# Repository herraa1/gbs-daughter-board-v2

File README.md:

# GBS Control Daughter Board v2

Enhance your [GBS8200](https://ramapcsx2.github.io/gbs-control/Wiki/Build-the-Hardware.html) upscaler board.

> [!WARNING]
> This is a work in progress project.
>
> An adapter based on PCB v2 Build1 has been successfully built
>
> No build instructions are yet provided
>

## Introduction

The GBS Daughter Board v2 is a companion board for the GBS8200 upscaler.
It facilitates the upgrade of an off-the-shelf GBS8200 board to a gbs-control firmware based solution, with the following main features:

* HAT-like design, simply stack the daughter board on top of the existing GBS8200
* add SCART RGB input
* add switchable HDMI output (via embedded VGA to HDMI dongle)
* add switchable sync stripper based on the LM1881
* add 3.5" jack sound output
* add switchable common or separate audio ground
* add auxiliar USB socket to optionally power external dongle
* add small OLED screen and rotary encoder for local control

## References

gbs-control
* https://github.com/ramapcsx2/gbs-control

GBS-C AIO
* https://github.com/amoore2600/GBS-C_AIO

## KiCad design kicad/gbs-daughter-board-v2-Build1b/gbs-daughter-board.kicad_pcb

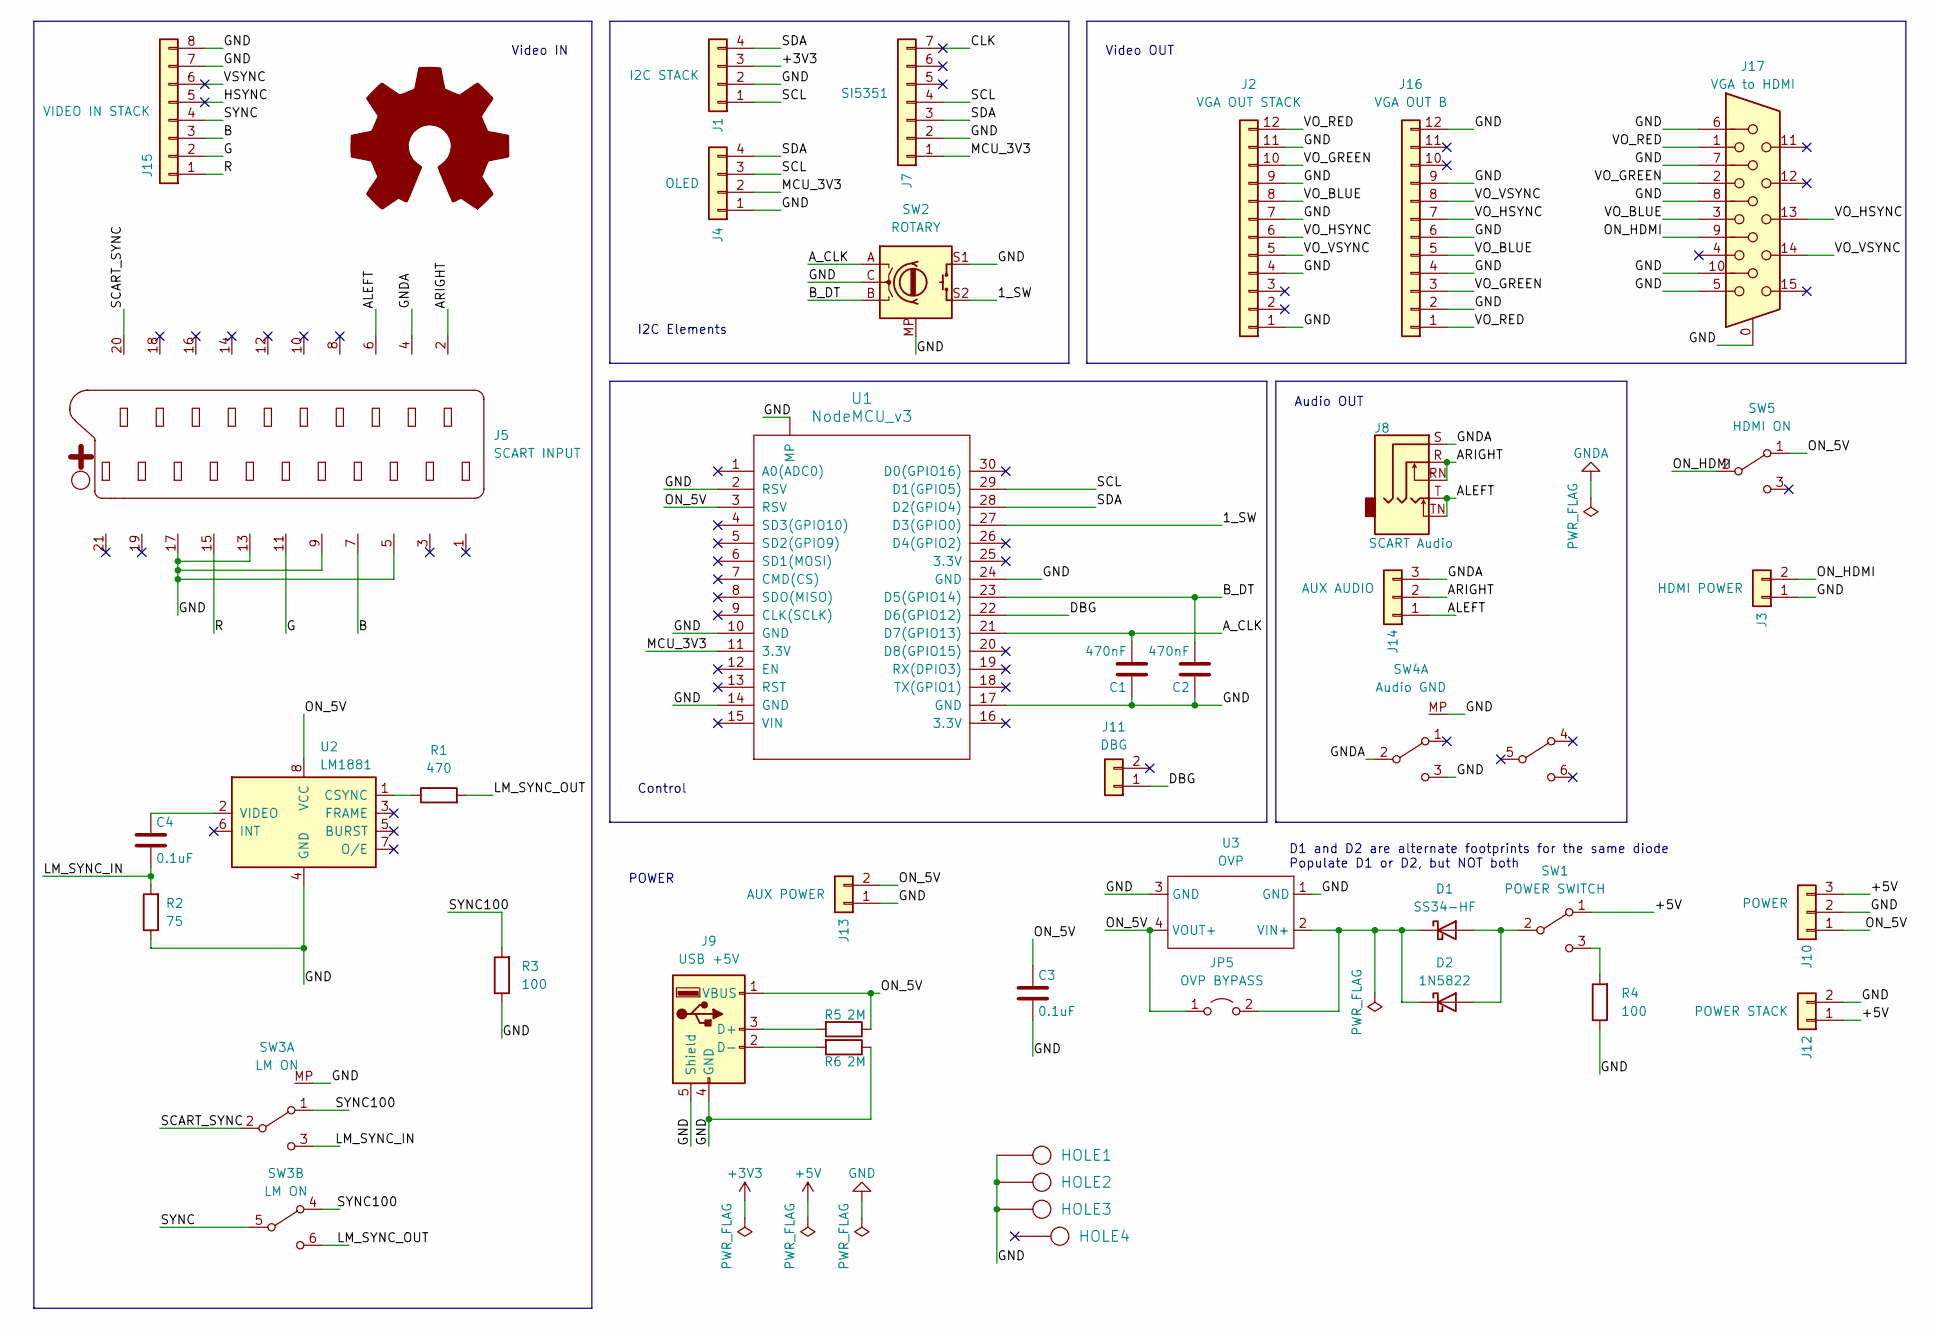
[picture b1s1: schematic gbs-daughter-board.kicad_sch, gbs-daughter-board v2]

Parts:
C1, C2: 470nF; Cap_Cer_508
C3, C4: 0.1uF; Cap_Cer_508
D1: SS34-HF; D_SMA_Handsoldering
D2: 1N5822; DIODE-DO-27-DO-201AD
HOLE1, HOLE2, HOLE3, HOLE4: HOLE; Hole_3mm
J1: I2C STACK; JST_XH_B4B-XH-A_1x04_P2.50mm_Vertical
J2: VGA OUT STACK; JST_PH_B12B-PH-K_1x12_P2.00mm_Vertical
J3: HDMI POWER; JST_XH_B2B-XH-A_1x02_P2.50mm_Vertical
J4: OLED; Display_128x64_096_I2C
J5: SCART INPUT; SCART
J7: SI5351; si5351a_Module
J8: SCART Audio; Jack_3.5mm_CUI_SJ1-3525N_Horizontal
J9: USB +5V; USB_A_CONNFLY_DS1095-WNR0
J10: POWER; JST_XH_S3B-XH-A_1x03_P2.50mm_Horizontal
J11: DBG; JST_XH_S2B-XH-A_1x02_P2.50mm_Horizontal
J12: POWER STACK; JST_XH_B2B-XH-A_1x02_P2.50mm_Vertical
J13: AUX POWER; JST_XH_B2B-XH-A_1x02_P2.50mm_Vertical
J14: AUX AUDIO; JST_XH_B3B-XH-A_1x03_P2.50mm_Vertical
J15: VIDEO IN STACK; Conn_1x08_P2.50mm
J16: VGA OUT B; JST_PH_S12B-PH-K_1x12_P2.00mm_Horizontal
J17: VGA to HDMI; DSUB-15-HD_Female_Horizontal_P2.29x1.98mm_EdgePinOffset3.03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
JP5: OVP BYPASS; Conn_Pin_Header_2x1_2.54mm_NoKey
R1: 470; Res_762
R2: 75; Res_762
R3, R4: 100; Res_762
R5, R6: 2M; Res_762
SW1: POWER SWITCH; SW_Toggle_Blue_wSlots
SW2: ROTARY; RotaryEncoder_Alps_EC11E-Switch_Vertical_H20mm_CircularMoun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
SW3: LM ON; SW_SK-22D07VG4-2P2T-4mm
SW4: Audio GND; SW_SK-22D07VG4-2P2T-4mm
SW5: HDMI ON; SW_SS-12D11
SYM1: Logo_Open_Hardware_Large; OSHW-Logo_7.5x8mm_SilkScreen
U1: NodeMCU_v3; NodeMCU-LoLinV3-LargePads
U2: LM1881; DIP-8_W7.62mm_Socket
U3: OVP; OVP_Module_5.5V_2.5A_30V

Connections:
+3V3: J1.3
+5V: J10.3, J12.1, SW1.1 (A)
/1_SW: SW2.S2, U1.27 (D3(GPIO0))
/ALEFT: J5.6, J8.T, J8.TN, J14.1
/ARIGHT: J5.2, J8.R, J8.RN, J14.2
/A_CLK: C1.2, SW2.A, U1.21 (D7(GPIO13))
/B: J5.7, J15.3
/B_DT: C2.2, SW2.B, U1.23 (D5(GPIO14))
/CLK: J7.7
/DBG: J11.1, U1.22 (D6(GPIO12))
/G: J5.11, J15.2
/HSYNC: J15.5
/LM_SYNC_IN: C4.2, R2.2, SW3.3 (C)
/LM_SYNC_OUT: R1.2, SW3.6 (C)
/MCU_3V3: J4.2, J7.1, U1.11 (3.3V)
/ON_5V: C3.1, J9.1 (VBUS), J10.1, J13.2, JP5.1 (A), R5.1, SW5.1 (A), U1.3 (RSV), U2.8 (VCC), U3.4 (VOUT+)
/ON_HDMI: J3.2, J17.9, SW5.2 (B)
/R: J5.15, J15.1
/SCART_SYNC: J5.20, SW3.2 (B)
/SCL: J1.1, J4.3, J7.4, U1.29 (D1(GPIO5))
/SDA: J1.4, J4.4, J7.3, U1.28 (D2(GPIO4))
/SYNC: J15.4, SW3.5 (B)
/SYNC100: R3.2, SW3.1 (A), SW3.4 (A)
/VO_BLUE: J2.8, J16.5, J17.3
/VO_GREEN: J2.10, J16.3, J17.2
/VO_HSYNC: J2.6, J16.7, J17.13
/VO_RED: J2.12, J16.1, J17.1
/VO_VSYNC: J2.5, J16.8, J17.14
/VSYNC: J15.6
GND: C1.1, C2.1, C3.2, HOLE1.1, HOLE2.1, HOLE3.1, J1.2, J2.1, J2.4, J2.7, J2.9, J2.11, J3.1, J4.1, J5.5, J5.9, J5.13, J5.17, J7.2, J9.4 (GND), J9.5 (Shield), J10.2, J12.2, J13.1, J15.7, J15.8, J16.2, J16.4, J16.6, J16.9, J16.12, J17.0, J17.5, J17.6, J17.7, J17.8, J17.10, R2.1, R3.1, R4.1, R6.1, SW2.C, SW2.MP, SW2.S1, SW3.MP, SW4.3 (C), SW4.MP, U1. (MP), U1.2 (RSV), U1.10 (GND), U1.14 (GND), U1.17 (GND), U1.24 (GND), U2.4 (GND), U3.1 (GND), U3.3 (GND)
GNDA: J5.4, J8.S, J14.3, SW4.2 (B)
unnamed: D1.2 (A), D2.2 (A), SW1.2 (B)
unnamed: D1.1 (K), D2.1 (K), JP5.2 (B), U3.2 (VIN+)
unnamed: J9.3 (D+), R5.2
unnamed: J9.2 (D-), R6.2
unnamed: R4.2, SW1.3 (C)
unnamed: R1.1, U2.1 (CSYNC)
unnamed: C4.1, U2.2 (VIDEO)

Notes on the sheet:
POWER
Control
I2C Elements
Video IN
Audio OUT
Video OUT
D1 and D2 are alternate footprints for the same diode Populate D1 or D2, but NOT both

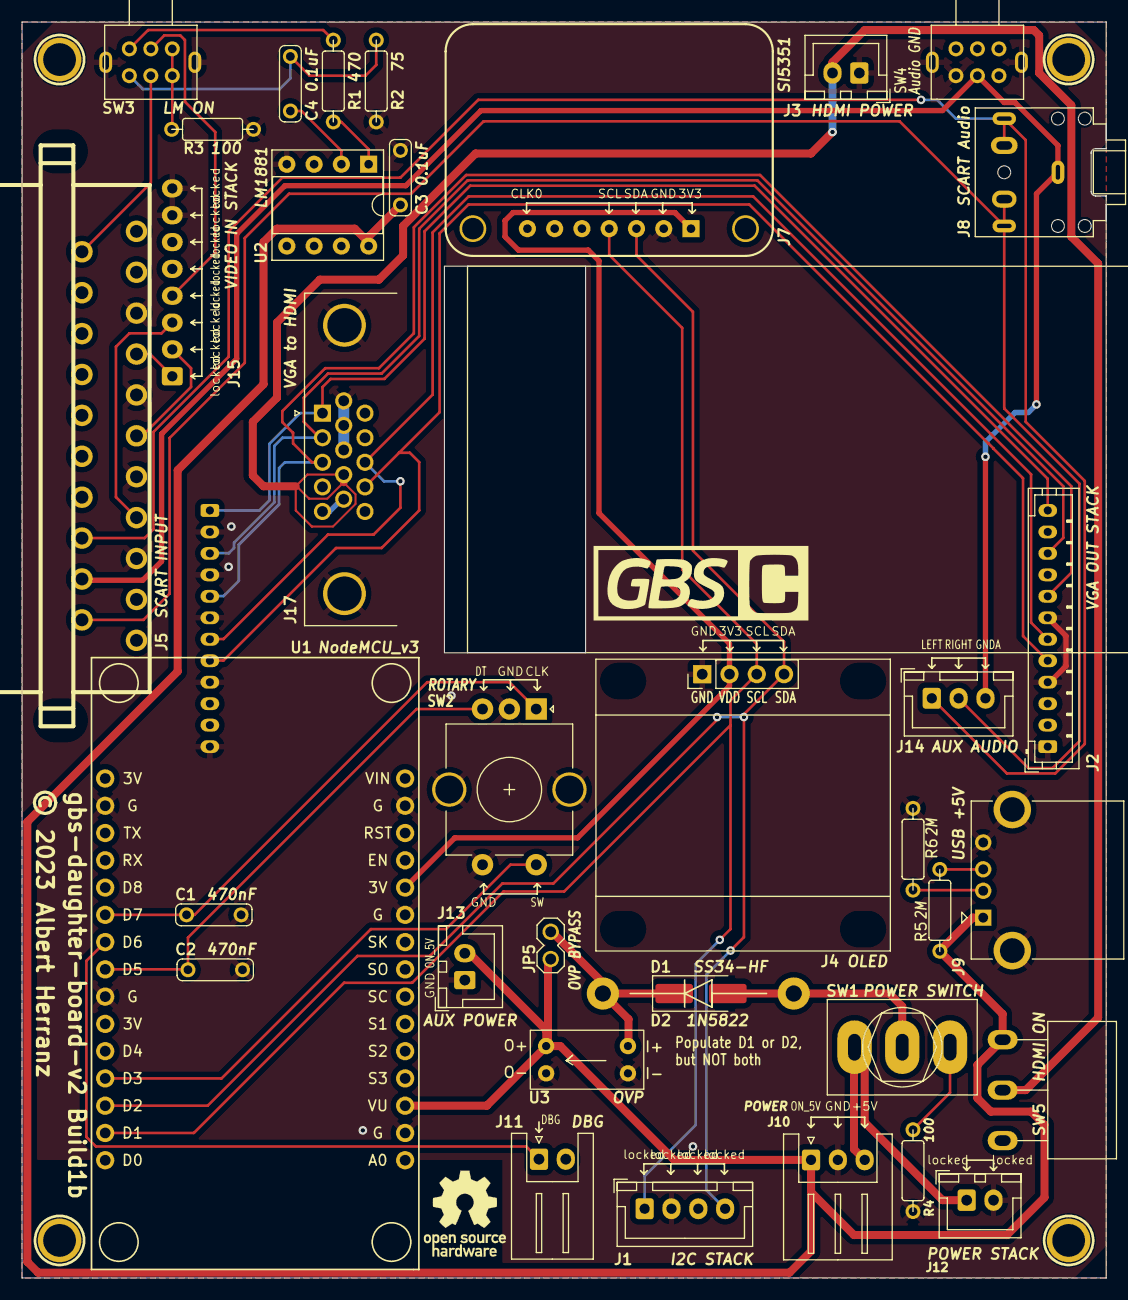
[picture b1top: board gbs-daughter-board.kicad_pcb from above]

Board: 2 copper layers, 101.0 x 117.0 mm, 42 parts (1 on the bottom side), 34 nets.

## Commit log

2024-02-29 Initial commit.

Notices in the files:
kicad/gbs-daughter-board-v2-Build1b/gbs-daughter-board.kicad_pcb:
© 2023 Albert Herranz
